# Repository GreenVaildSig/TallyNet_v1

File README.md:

# TallyNet_v1
Archive of my final exam piece TallyNet in version 1. This version contains many beginner errors and is not suitable for production. Hopfully all errors are eliminated in the new Version. All Texts are in German.

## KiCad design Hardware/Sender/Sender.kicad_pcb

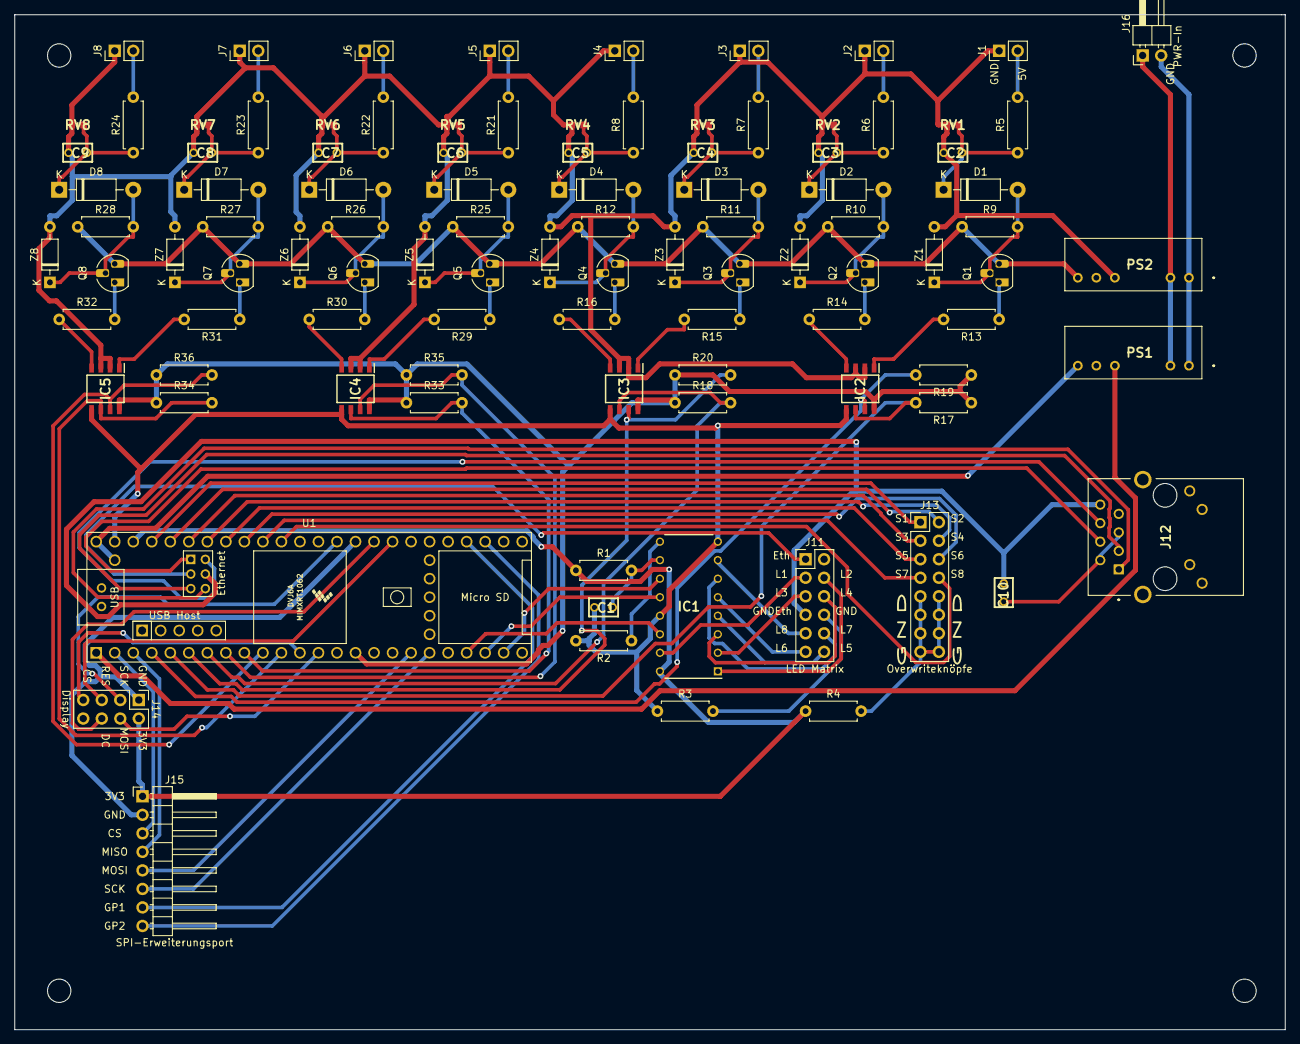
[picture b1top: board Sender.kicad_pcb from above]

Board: 2 copper layers, 174.2 x 139.2 mm, 104 parts (0 on the bottom side), 99 nets.

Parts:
C1, C2, C3, C4, C5, C6, C7, C8, C9, C10: 100nF; MONO-KAP_SIZE-15-L-5_
D1, D2, D3, D4, D5, D6, D7, D8: 1N4001; D_DO-41_SOD81_P10.16mm_Horizontal
IC1: SN74HC595N; DIP794W53P254L1930H508Q16N
IC2, IC3, IC4, IC5: HCPL-073L; SOIC127P599X361-8N
J1, J2, J3, J4, J5, J6, J7, J8: XLR3; PinHeader_1x02_P2.54mm_Vertical
J11: LED Matrix; PinHeader_2x06_P2.54mm_Vertical
J12: J1B1211CCD
J13: Overwriteknöpfe; PinHeader_2x08_P2.54mm_Vertical
J14: Display; PinHeader_2x04_P2.54mm_Vertical
J15: SPI-Erweiterungsport; PinHeader_1x08_P2.54mm_Horizontal
J16: PWR-In; PinHeader_1x02_P2.54mm_Horizontal
Moun4: MountingHole_3.2mm_M3
Mount1, Mount2, Mount3: MountingHole_3.2mm_M3
PS1, PS2: SPUN02M-05; SPUN02M05
Q1, Q2, Q3, Q4, Q5, Q6, Q7, Q8: BC327; TO-92_HandSolder
R1, R4: 330; R_Axial_DIN0207_L6.3mm_D2.5mm_P7.62mm_Horizontal
R2, R17, R18, R19, R20, R33, R34, R35, R36: 1K; R_Axial_DIN0207_L6.3mm_D2.5mm_P7.62mm_Horizontal
R3: 220; R_Axial_DIN0207_L6.3mm_D2.5mm_P7.62mm_Horizontal
R5, R6, R7, R8, R21, R22, R23, R24: 160; R_Axial_DIN0207_L6.3mm_D2.5mm_P7.62mm_Horizontal
R9, R10, R11, R12, R25, R26, R27, R28: 180; R_Axial_DIN0207_L6.3mm_D2.5mm_P7.62mm_Horizontal
R13, R14, R15, R16, R29, R30, R31, R32: 360; R_Axial_DIN0207_L6.3mm_D2.5mm_P7.62mm_Horizontal
RV1, RV2, RV3, RV4, RV5, RV6, RV7, RV8: EZJ-S1VB822; VARC1608X90N
U1: Teensy4.1; Teensy41
Z1, Z2, Z3, Z4, Z5, Z6, Z7, Z8: 1N5231BTR; D_DO-35_SOD27_P7.62mm_Horizontal

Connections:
3V3: IC1.16, J14.2, J15.1, R1.1, R4.1, U1.46
5VIC: PS1.7, U1.48, U1.49
5VTally: PS2.7, Q1.3, Q2.3, Q3.3, Q4.3, Q5.3, Q6.3, Q7.3, Q8.3, R9.1, R10.1, R11.1, R12.1, R25.1, R26.1, R27.1, R28.1
+12V: J16.2, PS1.1, PS2.1
/Eingangsschutzschaltung/3V3: IC2.8, IC3.8, IC4.8, IC5.8, R17.1, R18.1, R19.1, R20.1, R33.1, R34.1, R35.1, R36.1, U1.15
/Eingangsschutzschaltung/Tally1: IC2.7, R19.2, U1.4
/Eingangsschutzschaltung/Tally2: IC2.6, R17.2, U1.5
/Eingangsschutzschaltung/Tally3: IC3.7, R20.2, U1.6
/Eingangsschutzschaltung/Tally4: IC3.6, R18.2, U1.7
/Eingangsschutzschaltung/Tally5: IC4.7, R35.2, U1.8
/Eingangsschutzschaltung/Tally6: IC4.6, R33.2, U1.9
/Eingangsschutzschaltung/Tally7: IC5.7, R36.2, U1.10
/Eingangsschutzschaltung/Tally8: IC5.6, R34.2, U1.11
/Eingangsschutzschaltung/XLR1: J1.2, R5.2
/Eingangsschutzschaltung/XLR2: J2.2, R6.2
/Eingangsschutzschaltung/XLR3: J3.2, R7.2
/Eingangsschutzschaltung/XLR4: J4.2, R8.2
/Eingangsschutzschaltung/XLR5: J5.2, R21.2
/Eingangsschutzschaltung/XLR6: J6.2, R22.2
/Eingangsschutzschaltung/XLR7: J7.2, R23.2
/Eingangsschutzschaltung/XLR8: J8.2, R24.2
DISP-DC: J14.6, U1.33
DISP-Res: J14.5, U1.32
Eth_R+: J12.4, U1.60
Eth_R-: J12.6, U1.65
Eth_T+: J12.1, U1.63
Eth_T-: J12.3, U1.62
GND: J16.1, PS1.2, PS2.2
GND3V3: C1.2, IC1.8, IC1.13, IC2.5, IC3.5, IC4.5, IC5.5, R2.2, R3.1, U1.47
GNDEth: C10.2, J11.7, J12.8, U1.64
GNDIC: PS1.5, U1.1
GNDSPI: J14.1, J15.2, U1.34
GNDTally: C2.2, C3.2, C4.2, C5.2, C6.2, C7.2, C8.2, C9.2, IC2.2, IC2.3, IC3.2, IC3.3, IC4.2, IC4.3, IC5.2, IC5.3, J1.1, J2.1, J3.1, J4.1, J5.1, J6.1, J7.1, J8.1, PS2.5, RV1.2, RV2.2, RV3.2, RV4.2, RV5.2, RV6.2, RV7.2, RV8.2, Z1.2, Z2.2, Z3.2, Z4.2, Z5.2, Z6.2, Z7.2, Z8.2
unnamed: C1.1, IC1.10, R1.2
unnamed: C2.1, D1.1, R5.1, RV1.1
unnamed: C3.1, D2.1, R6.1, RV2.1
unnamed: C4.1, D3.1, R7.1, RV3.1
unnamed: C5.1, D4.1, R8.1, RV4.1
unnamed: C6.1, D5.1, R21.1, RV5.1
unnamed: C7.1, D6.1, R22.1, RV6.1
unnamed: C8.1, D7.1, R23.1, RV7.1
unnamed: C9.1, D8.1, R24.1, RV8.1
unnamed: C10.1, J12.2, J12.5
unnamed: D1.2, Q1.2, R9.2, Z1.1
unnamed: D2.2, Q2.2, R10.2, Z2.1
unnamed: D3.2, Q3.2, R11.2, Z3.1
unnamed: D4.2, Q4.2, R12.2, Z4.1
unnamed: D5.2, Q5.2, R25.2, Z5.1
unnamed: D6.2, Q6.2, R26.2, Z6.1
unnamed: D7.2, Q7.2, R27.2, Z7.1
unnamed: D8.2, Q8.2, R28.2, Z8.1
unnamed: IC1.1, J11.4
unnamed: IC1.2, J11.5
unnamed: IC1.3, J11.6
unnamed: IC1.4, J11.12
unnamed: IC1.5, J11.11
unnamed: IC1.6, J11.10
unnamed: IC1.7, J11.9
unnamed: IC1.9, R2.1
unnamed: IC1.11, U1.23
unnamed: IC1.12, U1.22
unnamed: IC1.14, U1.21
unnamed: IC1.15, J11.3
unnamed: IC2.1, R13.2
unnamed: IC2.4, R14.1
unnamed: IC3.1, R15.2
unnamed: IC3.4, R16.1
unnamed: IC4.1, R29.2
unnamed: IC4.4, R30.1
unnamed: IC5.1, R31.2
unnamed: IC5.4, R32.1
unnamed: J11.1, U1.61
unnamed: J11.8, R3.2
unnamed: J13.1, U1.45
unnamed: J13.2, U1.44
unnamed: J13.3, U1.43
unnamed: J13.4, U1.42
unnamed: J13.5, U1.41
unnamed: J13.6, U1.40
unnamed: J13.7, U1.39
unnamed: J13.8, U1.38
unnamed: J13.9, J13.10, J13.11, J13.12, J13.13, J13.14, J13.15, J13.16, R4.2
unnamed: J15.7, U1.28
unnamed: J15.8, U1.27
unnamed: Q1.1, R13.1
unnamed: Q2.1, R14.2
unnamed: Q3.1, R15.1
unnamed: Q4.1, R16.2
unnamed: Q5.1, R29.1
unnamed: Q6.1, R30.2
unnamed: Q7.1, R31.1
unnamed: Q8.1, R32.2
SPI0-CS0: J14.7, U1.12
SPI0-MOSI: J14.4, U1.13
SPI0-SCK: J14.3, U1.35
SPI1-CS1: J15.3, U1.2
SPI1-MISO: J15.4, U1.3
SPI1-MOSI: J15.5, U1.18
SPI1-SCK: J15.6, U1.19

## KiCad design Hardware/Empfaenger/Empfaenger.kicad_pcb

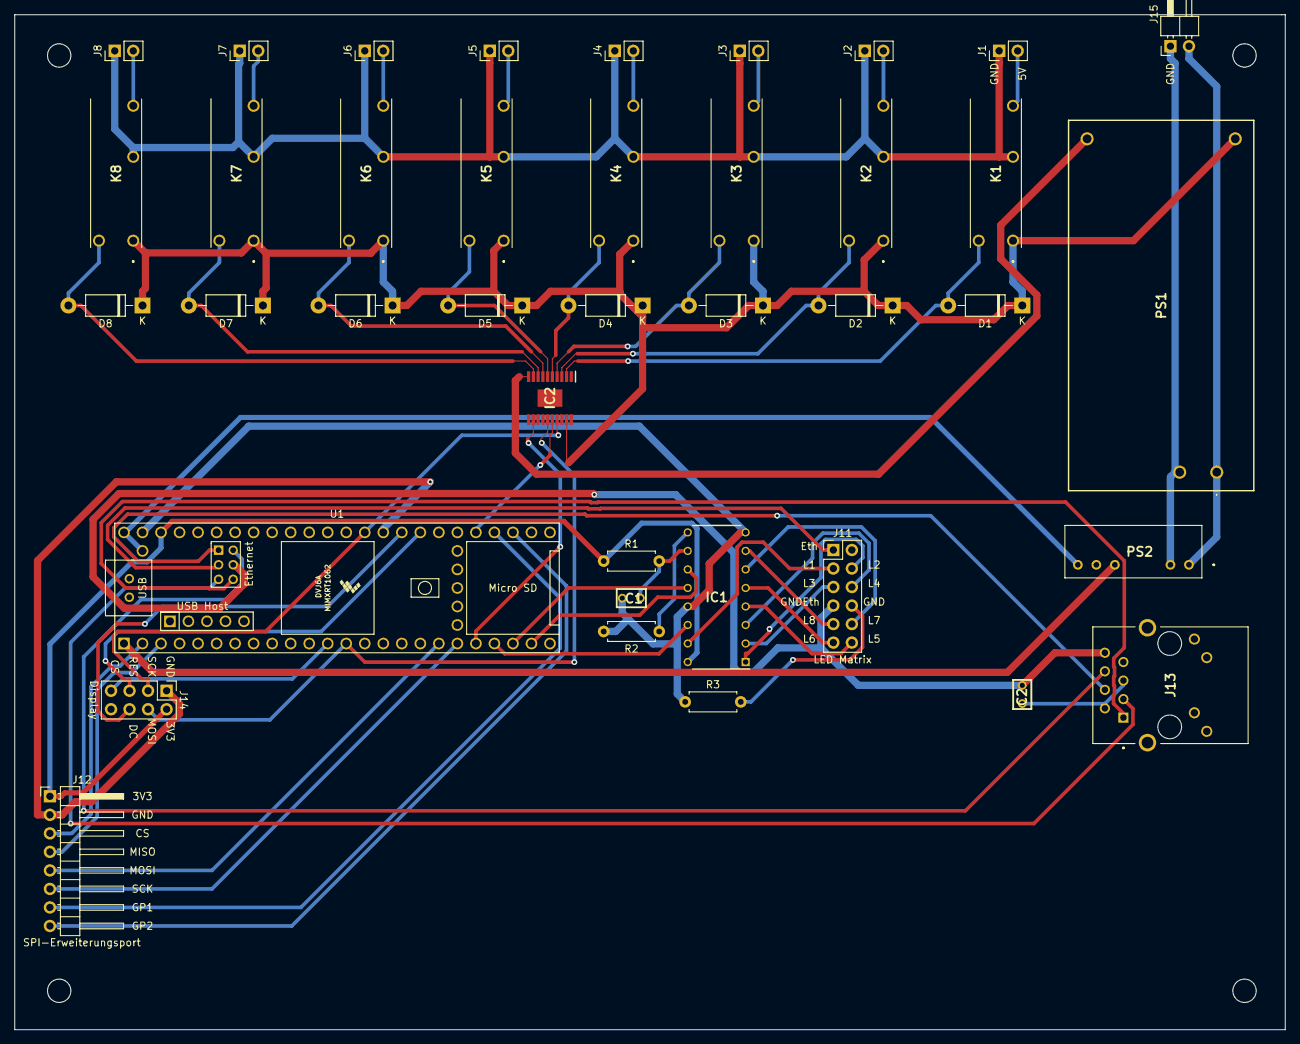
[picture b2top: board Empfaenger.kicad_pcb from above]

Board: 2 copper layers, 174.2 x 139.2 mm, 43 parts (0 on the bottom side), 60 nets.

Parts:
C1, C2: 100nF; MONO-KAP_SIZE-15-L-5_
D1, D2, D3, D4, D5, D6, D7, D8: 1N4007; D_DO-41_SOD81_P10.16mm_Horizontal
IC1: SN74HC595N; DIP794W53P254L1930H508Q16N
IC2: TPL9202PWP; SOP65P640X120-21N
J1, J2, J3, J4, J5, J6, J7, J8: XLR3; PinHeader_1x02_P2.54mm_Vertical
J11: LED Matrix; PinHeader_2x06_P2.54mm_Vertical
J12: SPI-Erweiterungsport; PinHeader_1x08_P2.54mm_Horizontal
J13: J1B1211CCD
J14: Display; PinHeader_2x04_P2.54mm_Vertical
J15: PWR-In; PinHeader_1x02_P2.54mm_Horizontal
K1, K2, K3, K4, K5, K6, K7, K8: G5NB-1A-HA_DC12; G5NB1AHADC12
Moun4: MountingHole_3.2mm_M3
Mount1, Mount2, Mount3: MountingHole_3.2mm_M3
PS1: MDS20A-12; MDS20A12
PS2: SPUN02M-05; SPUN02M05
R1: 330; R_Axial_DIN0207_L6.3mm_D2.5mm_P7.62mm_Horizontal
R2: 1K; R_Axial_DIN0207_L6.3mm_D2.5mm_P7.62mm_Horizontal
R3: 220; R_Axial_DIN0207_L6.3mm_D2.5mm_P7.62mm_Horizontal
U1: Teensy4.1; Teensy41

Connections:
3V3: IC1.16, J12.1, J14.2, R1.1, U1.46
5VIC: PS2.7, U1.48, U1.49
12V: D1.1, D2.1, D3.1, D4.1, D5.1, D6.1, D7.1, D8.1, IC2.19, K1.1, K2.1, K3.1, K4.1, K5.1, K6.1, K7.1, K8.1, PS1.3
+12V: J15.2, PS1.1, PS2.1
/Tallyausgangsschaltung/EN1: IC2.12, U1.20
/Tallyausgangsschaltung/Tally1: J1.2, K1.3
/Tallyausgangsschaltung/Tally2: J2.2, K2.3
/Tallyausgangsschaltung/Tally3: J3.2, K3.3
/Tallyausgangsschaltung/Tally4: J4.2, K4.3
/Tallyausgangsschaltung/Tally5: J5.2, K5.3
/Tallyausgangsschaltung/Tally6: J6.2, K6.3
/Tallyausgangsschaltung/Tally7: J7.2, K7.3
/Tallyausgangsschaltung/Tally8: J8.2, K8.3
DISP-DC: J14.6, U1.33
DISP-Res: J14.5, U1.32
Eth_R+: J13.4, U1.60
Eth_R-: J13.6, U1.65
Eth_T+: J13.1, U1.63
Eth_T-: J13.3, U1.62
GND: J15.1, PS1.2, PS2.2
GND3V3: C1.2, IC1.8, IC1.13, R2.2, R3.1, U1.47
GND12V: IC2.10, PS1.5
GNDEth: C2.2, J11.7, J13.8, U1.64
GNDIC: PS2.5, U1.1
GNDSPI: J12.2, J14.1, U1.34
GNDTally: J1.1, J2.1, J3.1, J4.1, J5.1, J6.1, J7.1, J8.1, K1.2, K2.2, K3.2, K4.2, K5.2, K6.2, K7.2, K8.2
unnamed: C1.1, IC1.10, R1.2
unnamed: C2.1, J13.2, J13.5
unnamed: D1.2, IC2.2, K1.4
unnamed: D2.2, IC2.3, K2.4
unnamed: D3.2, IC2.4, K3.4
unnamed: D4.2, IC2.5, K4.4
unnamed: D5.2, IC2.6, K5.4
unnamed: D6.2, IC2.7, K6.4
unnamed: D7.2, IC2.8, K7.4
unnamed: D8.2, IC2.9, K8.4
unnamed: IC1.1, J11.4
unnamed: IC1.2, J11.5
unnamed: IC1.3, J11.6
unnamed: IC1.4, J11.12
unnamed: IC1.5, J11.11
unnamed: IC1.6, J11.10
unnamed: IC1.7, J11.9
unnamed: IC1.9, R2.1
unnamed: IC1.11, U1.23
unnamed: IC1.12, U1.22
unnamed: IC1.14, U1.21
unnamed: IC1.15, J11.3
unnamed: J11.1, U1.61
unnamed: J11.8, R3.2
unnamed: J12.7, U1.28
unnamed: J12.8, U1.27
SPI0-CS0: J14.7, U1.12
SPI0-CS1: IC2.16, U1.29
SPI0-MOSI: IC2.15, J14.4, U1.13
SPI0-SCK: IC2.17, J14.3, U1.35
SPI1-CS1: J12.3, U1.2
SPI1-MISO: J12.4, U1.3
SPI1-MOSI: J12.5, U1.18
SPI1-SCK: J12.6, U1.19

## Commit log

2022-08-05 Dokumentation und Anlagen hinzugefügt
2022-08-05 Gehäuse Daten
2022-08-05 Software v1
2022-08-05 KiCAD Dateien
